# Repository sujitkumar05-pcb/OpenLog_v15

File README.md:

# OpenLog_v15

## 1. Project Overview
OpenLog_v15 is a compact data logging system designed to record serial data onto a microSD card in a simple and reliable manner. It is commonly used for debugging, sensor data logging, and embedded system development. The module interfaces easily with microcontrollers via UART and operates with minimal configuration, making it suitable for both prototyping and long-term data collection applications.

-----

## 2. Key Learning Objectives

Understand serial (UART) communication and data logging concepts.

Learn how to interface a microSD card with embedded systems.

Gain experience in reliable data storage for debugging and monitoring.

Understand low-power, standalone logging module design.

Develop skills for integrating logging modules with microcontrollers.
-----

## 3. Tools & Software Used
- **KiCad EDA**
  - Schematic Editor  
  - PCB Layout Editor  
  - 3D Viewer
 
 ---

## 4. Project Files
- Schematic design files (`.kicad_sch`)  
- PCB layout files (`.kicad_pcb`)  
- 3D render images  
- Manufacturing-ready Gerber files  

---

## 5. Block-Level Working Explanation

Microcontroller (UART TX): Sends serial data to the OpenLog module.

UART Interface: Receives and transfers data reliably to the logger.

OpenLog Controller: Processes incoming data and manages file operations.

microSD Card: Stores the received data as sequential log files.

Power Supply Block: Provides regulated voltage for stable operation.

## 6. Bill of Materials (BOM)
|Sno.| Reference      | Qty | Value / Part            | Footprint                                                  |
| -- | -------------- | --- | ----------------------- | ---------------------------------------------------------- |
| 1  | C1             | 1   | 10 µF                   | Capacitor_SMD:C_1206_3216Metric                            |
| 2  | C2, C3         | 2   | 0.1 µF                  | Capacitor_SMD:C_1206_3216Metric                            |
| 3  | C4             | 1   | 0.1 µF                  | Capacitor_SMD:C_1210_3225Metric                            |
| 4  | D1             | 1   | Green LED               | LED_SMD:LED_0805_2012Metric                                |
| 5  | D2             | 1   | Blue LED                | LED_SMD:LED_0805_2012Metric                                |
| 6  | H1, H2, H3, H4 | 4   | Mounting Hole           | MountingHole:MountingHole_2.1mm                            |
| 7  | J1             | 1   | Pin Header 1×4          | Connector_PinHeader_2.54mm:PinHeader_1x04_P2.54mm_Vertical |
| 8  | J2             | 1   | Pin Header 1×6          | Connector_PinHeader_2.54mm:PinHeader_1x06_P2.54mm_Vertical |
| 9  | J3             | 1   | Micro SD Card Connector | Connector_Card:microSD_HC_Hirose_DM3AT-SF-PEJM5            |
| 10 | Q1             | 1   | 16 MHz Crystal          | Crystal:Crystal_SMD_MicroCrystal_MS1V-T1K                  |
| 11 | R1             | 1   | 330 Ω                   | Resistor_SMD:R_0805_2012Metric                             |
| 12 | R2, R3         | 2   | 1 kΩ                    | Resistor_SMD:R_0805_2012Metric                             |
| 13 | TP1            | 1   | Test Point              | Connector_PinHeader_1.27mm:PinHeader_1x01_P1.27mm_Vertical |
| 14 | U1             | 1   | MIC5205 (3.3 V LDO)     | Package_TO_SOT_SMD:SOT-23-5                                |
| 15 | U2             | 1   | ATmega328P-A            | Package_QFP:TQFP-32_7x7mm_P0.8mm                           |

## 7. Images & Renders

- **Schematic**

- **PCB Layout**

- **3D View**

---

## 8. Disclaimer
This project is intended for educational and experimental purposes only. While the design follows standard engineering practices, it should be carefully reviewed and tested before use in real-world applications. The author is not responsible for any damage, data loss, or issues arising from improper use or modification of this design.
---

## 9. Author
- **Name:** SUJIT KUMAR
- **Toolchain:** KiCad EDA

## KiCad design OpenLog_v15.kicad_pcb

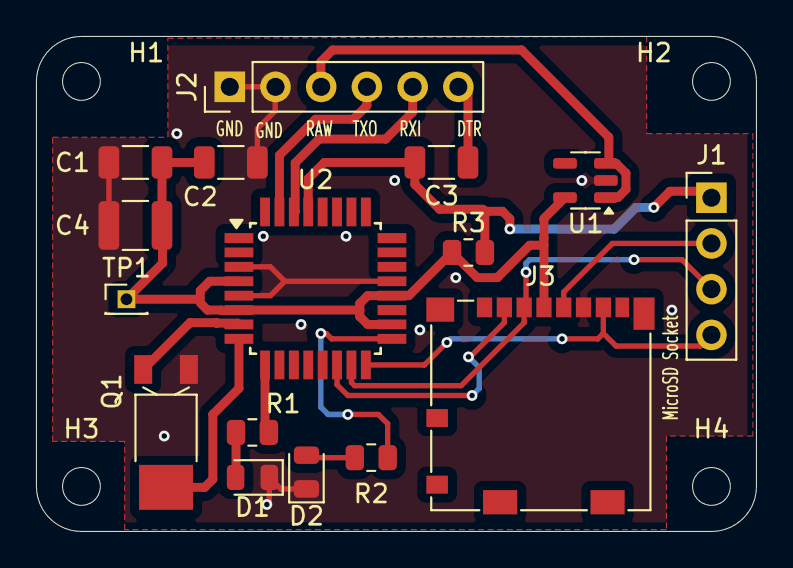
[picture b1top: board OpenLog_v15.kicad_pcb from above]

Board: 2 copper layers, 40.0 x 27.5 mm, 20 parts (0 on the bottom side), 17 nets.

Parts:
C1: 10uF; C_1206_3216Metric
C2, C3: 0.1uF; C_1206_3216Metric
C4: 0.1uF; C_1210_3225Metric
D1: GREEN; LED_0805_2012Metric
D2: BLUE; LED_0805_2012Metric
H1, H2, H3, H4: MountingHole; MountingHole_2.1mm
J1: PinHeader_1x04_P2.54mm_Vertical
J2: Conn_01x06_Pin; PinHeader_1x06_P2.54mm_Vertical
J3: Micro_SD_Card; microSD_HC_Molex_104031-0811
Q1: 16MHZ; Crystal_SMD_MicroCrystal_MS1V-T1K
R1: 330; R_0805_2012Metric
R2, R3: 1K; R_0805_2012Metric
TP1: PinHeader_1x01_P1.27mm_Vertical
U1: 3.3V MIC5205; SOT-23-5
U2: ATmega328P-A; TQFP-32_7x7mm_P0.8mm

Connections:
3.3V: C1.1, C2.1, C4.2, J3.4 (VCC), R3.1, TP1.1, U1.5 (OUT), U2.4 (VCC), U2.6 (VCC), U2.18 (AVCC), U2.20 (AREF)
CS: J3.2 (CS), U2.14 (PB2(SS/OC1B))
DTR: C3.1, J2.6
GND: C1.2, C2.2, C4.1, D1.1 (K), D2.1 (K), J2.1, J2.2, J3.6 (GND), Q1.2, U1.2 (GND), U2.3 (GND), U2.5 (GND), U2.21 (AGND)
MISO: J1.4, J3.7 (DO), U2.16 (PB4(MISO))
MOSI: J1.3, J3.3 (DI), U2.15 (PB3(MOSI/OC2))
unnamed: D1.2 (A), R1.2
unnamed: D2.2 (A), R2.2
unnamed: R2.1, U2.17 (PB5(SCK))
unnamed: Q1.1, U2.7 (PB6/XTAL1)
unnamed: Q1.3, U2.8 (PB7/XTAL2)
unnamed: R1.1, U2.9 (PD5(T1))
RAW: J2.3, U1.1 (IN), U1.3 (EN)
RST: C3.2, J1.1, R3.2, U2.29 (PC6/~RESET)
RXI: J2.5, U2.30 (PD0(RDX))
SCK: J1.2, J3.5 (SCK)
TXO: J2.4, U2.31 (PD1(TXD))
